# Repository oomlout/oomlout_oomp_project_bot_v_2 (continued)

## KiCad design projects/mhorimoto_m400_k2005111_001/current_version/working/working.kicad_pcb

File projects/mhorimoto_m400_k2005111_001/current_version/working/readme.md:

# m400_k2005111
 
## summary 
* id: mhorimoto_m400_k2005111_001
* user: mhorimoto
* name: m400_k2005111
* board: 001
* repo: https://github.com/mhorimoto/M400-k2005111
* src_file_repo_kicad_pcb: 001.kicad_pcb
* src_file_repo_kicad_pcb_link: https://github.com/mhorimoto/M400-k2005111/tree/master/001.kicad_pcb

* src_file_repo_sch: 001.sch
* src_file_repo_sch_link: https://github.com/mhorimoto/M400-k2005111/tree/master/001.sch
* full details link: https://github.com/oomlout/oomlout_oomp_project_bot_v_2/tree/main/projects/mhorimoto_m400_k2005111_001/current_version/working

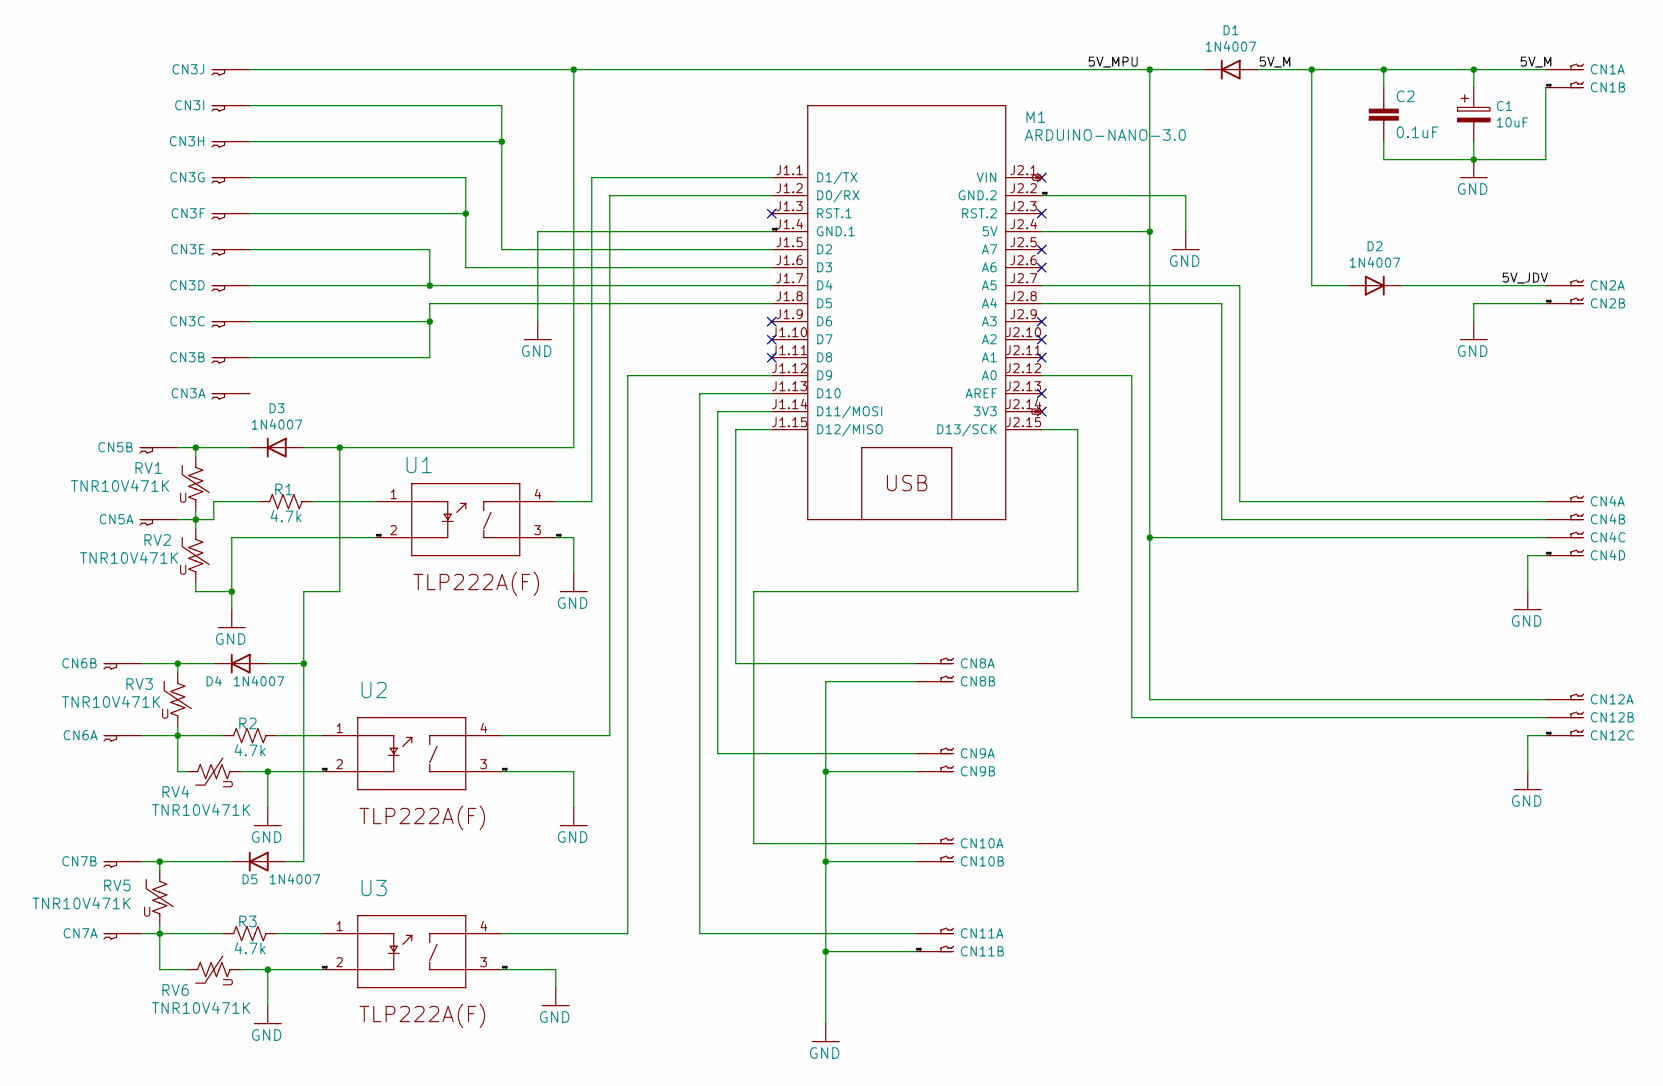
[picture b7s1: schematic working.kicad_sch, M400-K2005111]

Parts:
C1: 10uF; CP_Radial_D5.0mm_P2.00mm
C2: 0.1uF; C_Disc_D5.0mm_W2.5mm_P2.50mm
CN1: PWR5V; B02B-XH
CN2: JD-VCC; B02B-XH
CN3: TO-RLY; B10B-XH
CN4: I2C-LCD; B04B-XH
CN5: INPUT-A; B02B-XH
CN6: INPUT-B; B02B-XH
CN7: INPUT-C; B02B-XH
CN8: BTN-A; B02B-XH
CN9: BTN-B; B02B-XH
CN10: BTN-C; B02B-XH
CN11: BTN-STOP; B02B-XH
CN12: DELAY-VR; B03B-XH
D1, D2, D3, D4, D5: 1N4007; D_DO-41_SOD81_P10.16mm_Horizontal
M1: ARDUINO-NANO-3.0
R1, R2, R3: 4.7k; R_Axial_DIN0207_L6.3mm_D2.5mm_P10.16mm_Horizontal
RV1, RV2, RV3, RV4, RV5, RV6: TNR10V471K; RV_Disc_D12mm_W3.9mm_P7.5mm
U1, U2, U3: TOSHIBA_TLP222A; TOSHIBA_TLP222A_F_0

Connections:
3V3: M1.J2.14 (3V3)
/5V_JDV: CN2.P$1, D2.1 (K)
/5V_M: C1.1, C2.1, CN1.P$1, D1.2 (A), D2.2 (A)
/5V_MPU: CN3.P$10, CN4.P$3, CN12.P$1, D1.1 (K), D3.2 (A), D4.2 (A), D5.2 (A), M1.J2.4 (5V)
GND: C1.2, C2.2, CN1.P$2, CN2.P$2, CN4.P$4, CN8.P$2, CN9.P$2, CN10.P$2, CN11.P$2, CN12.P$3, M1.J1.4 (GND.1), M1.J2.2 (GND.2), RV2.2, RV4.2, RV6.2, U1.2 (CATHODE), U1.3 (1_DRAIN), U2.2 (CATHODE), U2.3 (1_DRAIN), U3.2 (CATHODE), U3.3 (1_DRAIN)
unnamed: CN3.P$2, CN3.P$3, M1.J1.8 (D5)
unnamed: CN3.P$4, CN3.P$5, M1.J1.7 (D4)
unnamed: CN3.P$6, CN3.P$7, M1.J1.6 (D3)
unnamed: CN3.P$8, CN3.P$9, M1.J1.5 (D2)
unnamed: CN4.P$1, M1.J2.7 (A5)
unnamed: CN4.P$2, M1.J2.8 (A4)
unnamed: CN5.P$1, R1.1, RV1.2, RV2.1
unnamed: CN5.P$2, D3.1 (K), RV1.1
unnamed: CN6.P$1, R2.1, RV3.2, RV4.1
unnamed: CN6.P$2, D4.1 (K), RV3.1
unnamed: CN7.P$1, R3.1, RV5.2, RV6.1
unnamed: CN7.P$2, D5.1 (K), RV5.1
unnamed: CN8.P$1, M1.J1.15 (D12/MISO)
unnamed: CN9.P$1, M1.J1.14 (D11/MOSI)
unnamed: CN10.P$1, M1.J2.15 (D13/SCK)
unnamed: CN11.P$1, M1.J1.13 (D10)
unnamed: CN12.P$2, M1.J2.12 (A0)
unnamed: M1.J1.1 (D1/TX), U1.4 (2_DRAIN)
unnamed: M1.J1.2 (D0/RX), U2.4 (2_DRAIN)
unnamed: M1.J1.12 (D9), U3.4 (2_DRAIN)
unnamed: R1.2, U1.1 (ANODE)
unnamed: R2.2, U2.1 (ANODE)
unnamed: R3.2, U3.1 (ANODE)
VIN: M1.J2.1 (VIN)

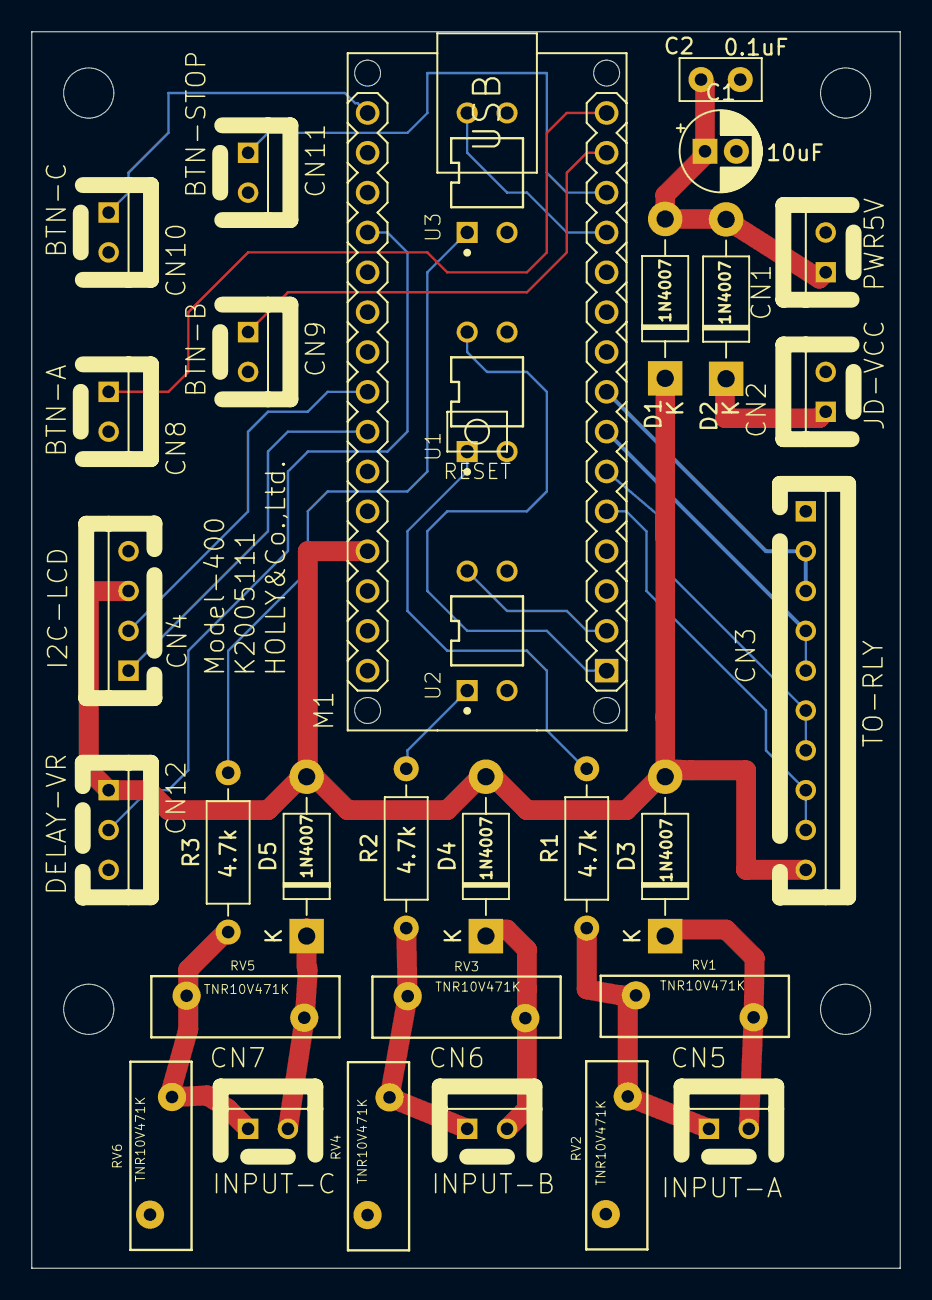
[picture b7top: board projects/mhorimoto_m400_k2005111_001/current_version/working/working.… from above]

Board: 2 copper layers, 55.4 x 78.8 mm, 32 parts (0 on the bottom side), 27 nets.

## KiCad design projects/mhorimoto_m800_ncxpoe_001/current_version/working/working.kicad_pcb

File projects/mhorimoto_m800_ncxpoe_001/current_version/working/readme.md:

# m800_ncxpoe
 
## summary 
* id: mhorimoto_m800_ncxpoe_001
* user: mhorimoto
* name: m800_ncxpoe
* board: 001
* repo: https://github.com/mhorimoto/M800-NCxPoE
* src_file_repo_kicad_pcb: 001.kicad_pcb
* src_file_repo_kicad_pcb_link: https://github.com/mhorimoto/M800-NCxPoE/tree/master/001.kicad_pcb

* src_file_repo_sch: 001.sch
* src_file_repo_sch_link: https://github.com/mhorimoto/M800-NCxPoE/tree/master/001.sch
* full details link: https://github.com/oomlout/oomlout_oomp_project_bot_v_2/tree/main/projects/mhorimoto_m800_ncxpoe_001/current_version/working

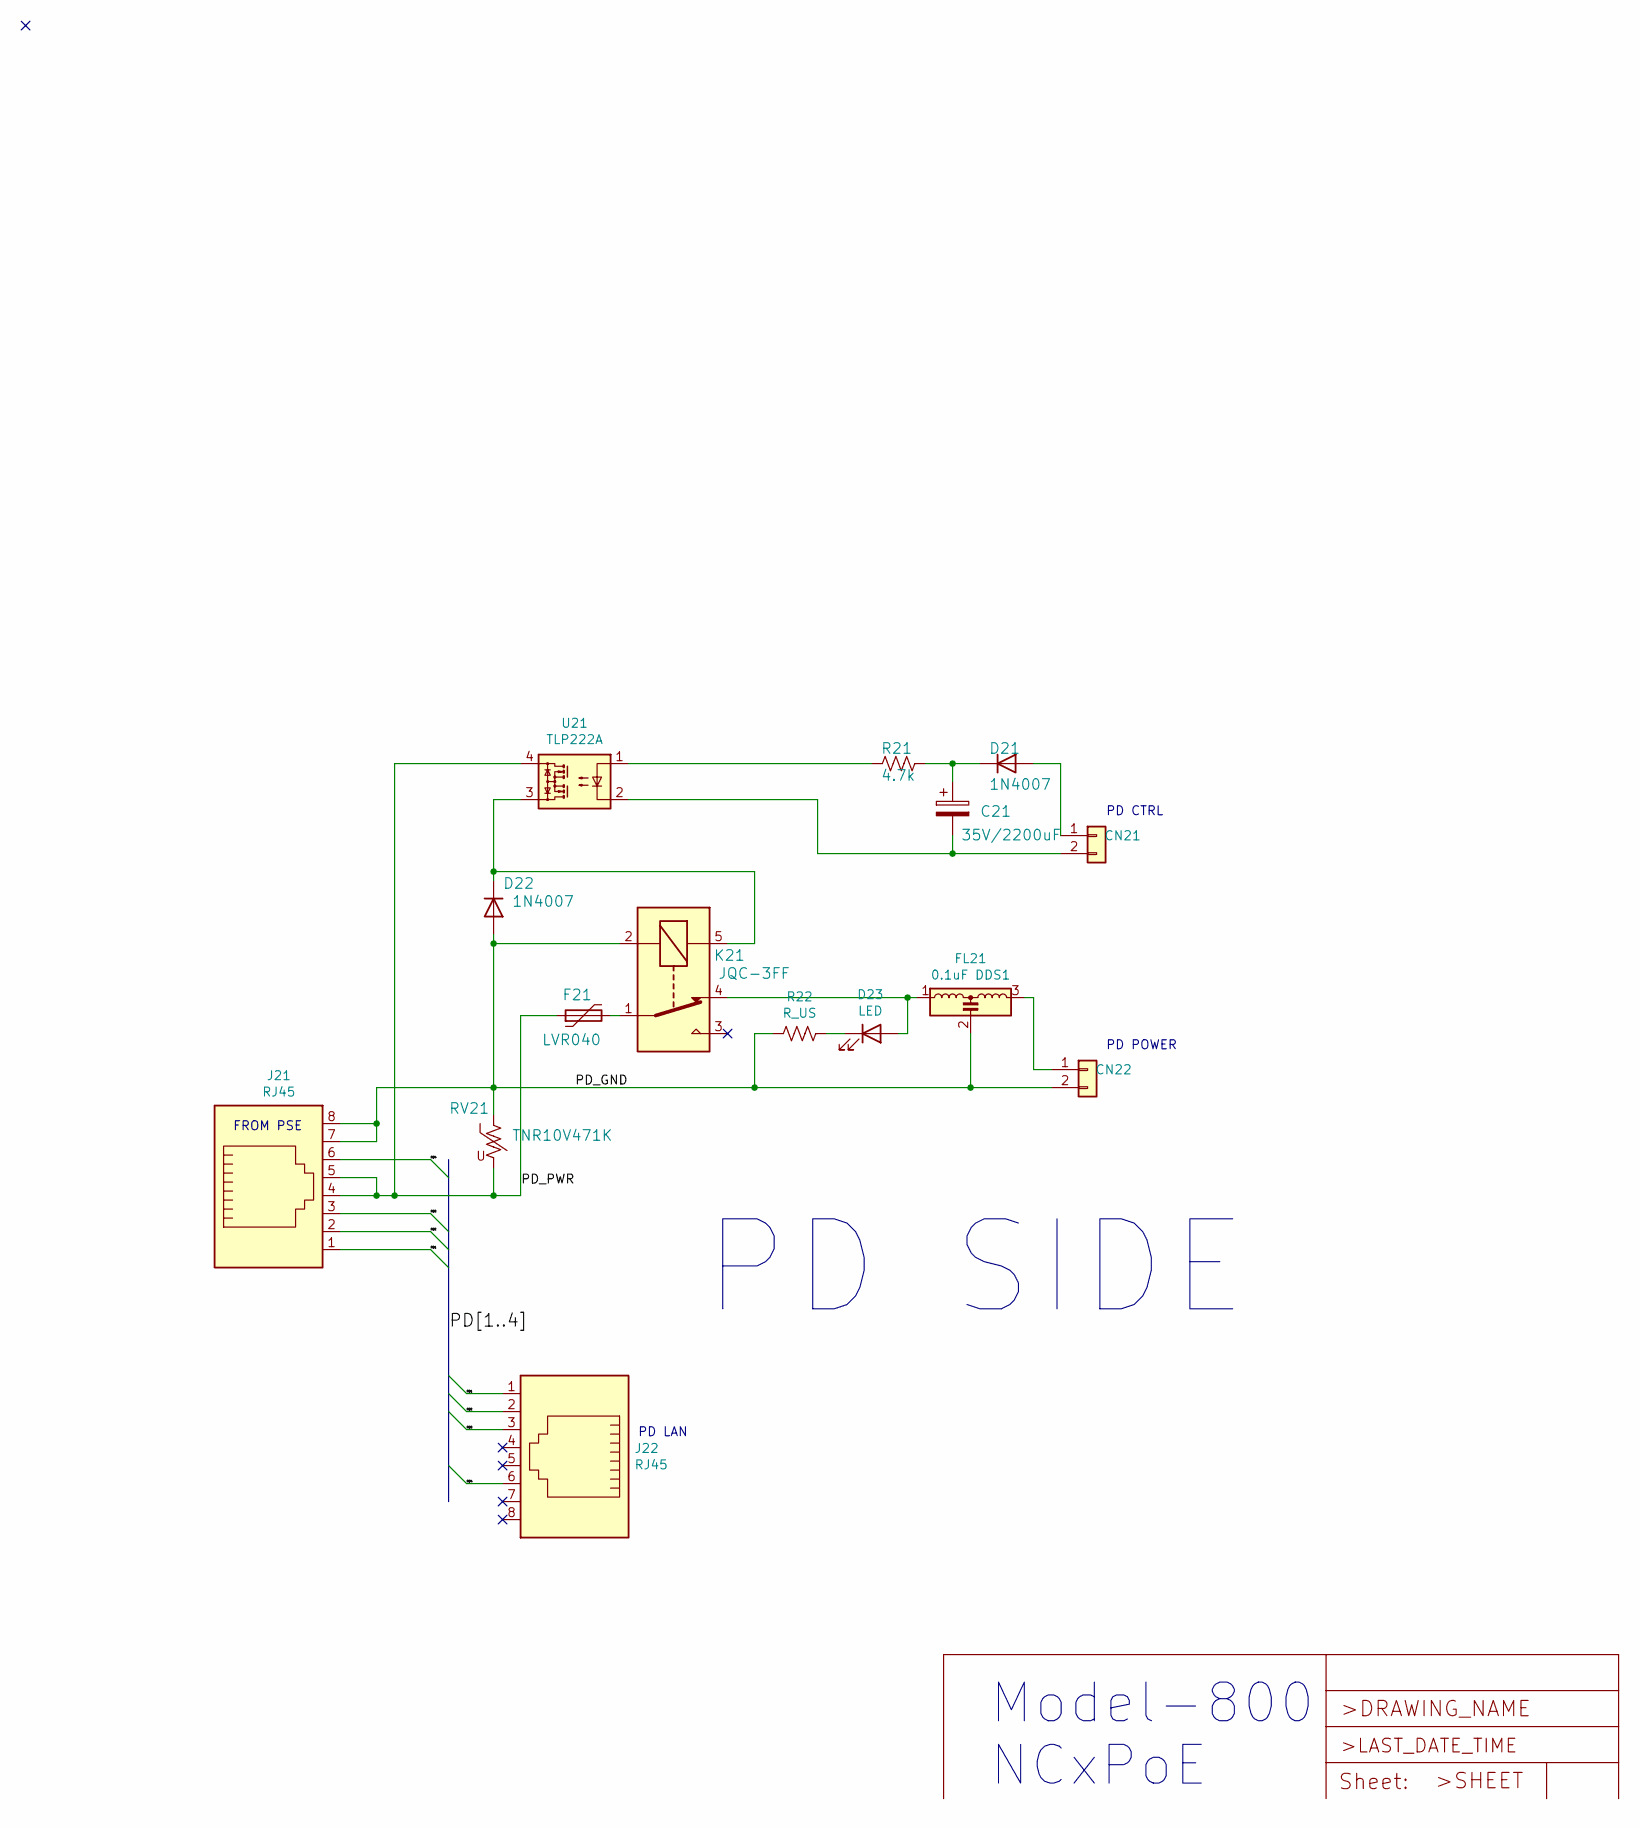
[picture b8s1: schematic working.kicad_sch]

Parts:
C21: 35V/2200uF; CP_Radial_D16.0mm_P7.50mm
CN21, CN22: 02-XH-A; JST_XH_B2B-XH-A_1x02_P2.50mm_Vertical
D21, D22: 1N4007; D_DO-41_SOD81_P10.16mm_Horizontal
D23: LED; LED_D3.0mm
F21: LVR040; Fuse_BelFuse_0ZRE0033FF_L11.4mm_W3.8mm
FL21: 0.1uF DDS1; DSS1
J21, J22: RJ45; RJ45_Neltron_7810-8P8C
K21: JQC-3FF; Relay_SPDT_Omron-G5LE-1
R21: 4.7k; R_Axial_DIN0207_L6.3mm_D2.5mm_P10.16mm_Horizontal
R22: R_US; R_Axial_DIN0207_L6.3mm_D2.5mm_P10.16mm_Horizontal
RV21: TNR10V471K; RV_Disc_D12mm_W3.9mm_P7.5mm
U21: TLP222A; DIP-4_W7.62mm

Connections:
/PD1: J21.1, J22.1
/PD2: J21.2, J22.2
/PD3: J21.3, J22.3
/PD4: J21.6, J22.6
/PD_GND: CN22.2, D22.2 (A), FL21.2, J21.7, J21.8, K21.2, R22.2, RV21.1
/PD_PWR: F21.1, J21.4, J21.5, RV21.2, U21.4
unnamed: C21.1, D21.1 (K), R21.1
unnamed: C21.2, CN21.2, U21.2
unnamed: CN21.1, D21.2 (A)
unnamed: CN22.1, FL21.3
unnamed: D22.1 (K), K21.5, U21.3
unnamed: D23.1 (K), R22.1
unnamed: D23.2 (A), FL21.1, K21.4
unnamed: F21.2, K21.1
unnamed: R21.2, U21.1

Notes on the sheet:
PD POWER
PD CTRL
PD SIDE
PD LAN
FROM PSE
Model-800 NCxPoE

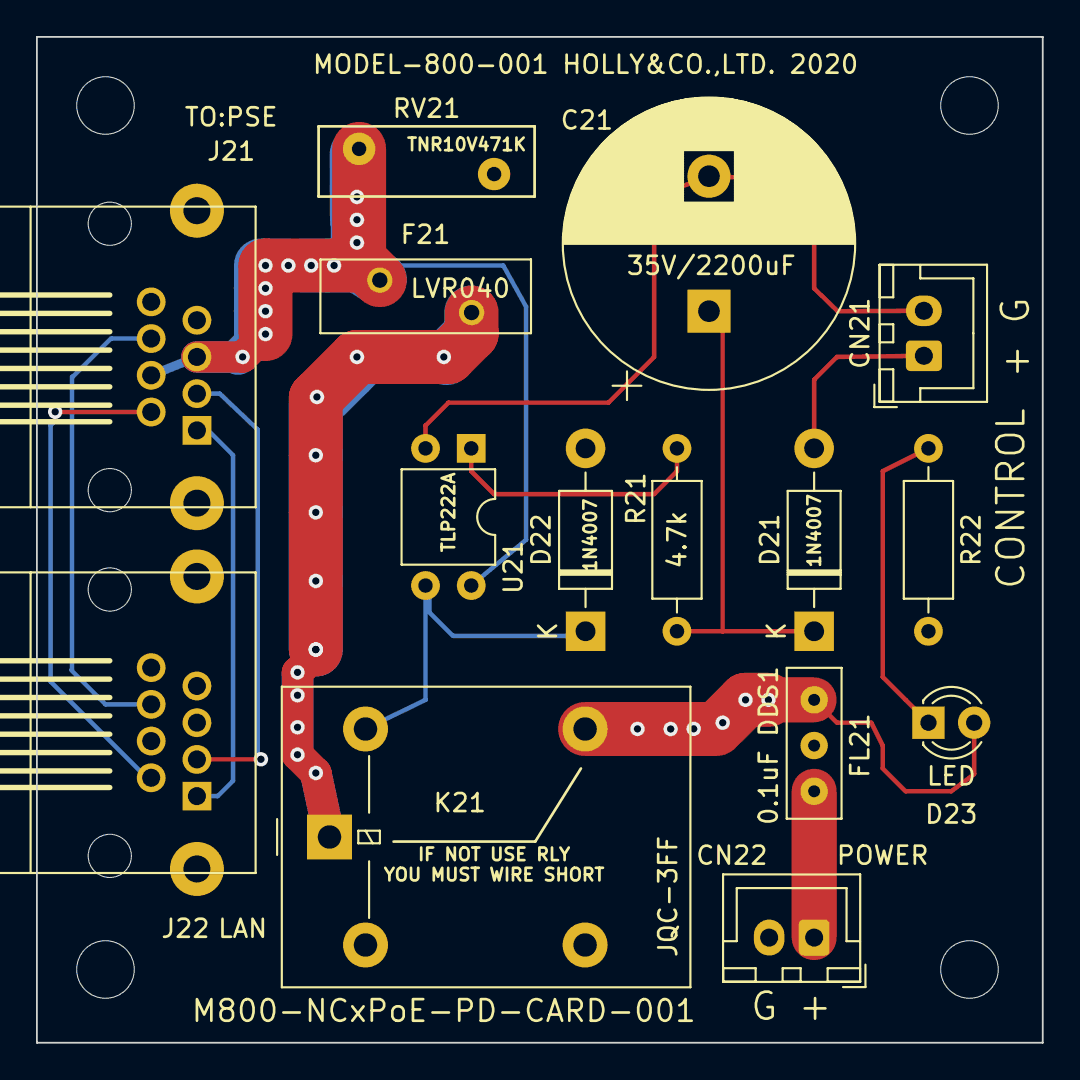
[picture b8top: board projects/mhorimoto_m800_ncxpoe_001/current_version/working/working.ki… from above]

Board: 2 copper layers, 55.9 x 55.9 mm, 15 parts (0 on the bottom side), 15 nets.
